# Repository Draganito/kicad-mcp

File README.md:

# kicad-mcp

I built this because I needed a replacement LED panel for my
**Beseler 4×5** enlarger (MILUKA Aristo D2). I had never designed a
PCB, and I did not want to learn KiCad by clicking through menus.

So you keep **KiCad** open. In **Cursor** you tell an assistant what
the board should be — in plain language. It downloads the real JLCPCB
parts, places them, assigns the nets, pours the copper, checks its own
work, and writes the files JLCPCB actually accepts.

This is not a second PCB editor and not “chat, invent a `.kicad_pcb`”.
KiCad stays the source of truth. Every change is **Ctrl+Z**. Nothing
is saved unless you ask.

**Proof it works:** the board that started it —
[contrib/aristo-d2-led-panel](contrib/aristo-d2-led-panel), 109 SK6812
LEDs, 4 layers, designed this way from the first outline to the
ordered Gerbers, manufactured by JLCPCB.

**Work in progress:**
[contrib/aristo-d2-led-panel-v2](contrib/aristo-d2-led-panel-v2) —
112× WS2812B-MINI drop-in. Layout and gerbers only; not a build guide.

**Docs:** [Install on Debian](docs/INSTALL_DEBIAN.md) ·
[Manual (A–Z reference)](docs/MANUAL.md)

---

## Who this is for

Students, hobbyists, makers on **Debian/Ubuntu** who want help with
the boring bits: a LED grid, wire pads, a GND pour, Gerbers that
JLCPCB accepts — without learning a pro tool first.

You still decide the circuit. The assistant must not invent pin
functions — those come from the LCSC / EasyEDA part, and built-in
checks (`check_pins`, `check_placement`, `review_board`) force it to
account for every pin instead of hand-waving.

Skip this if you layout in Altium, only have Windows, or do not want
an assistant in the editor at all.

---

## What you need

- A PC with Debian or Ubuntu (x86-64)
- [KiCad 10](https://www.kicad.org/download/linux/) — not Debian’s
  KiCad 9
- [Cursor](https://cursor.com)
- An LCSC part number when you want a real JLCPCB footprint
  (e.g. `C14663` for an 0603 cap)

---

## Install

1. Download the latest `kicad-mcp_*.deb` from
   **[Releases](https://github.com/Draganito/kicad-mcp/releases)**.
2. Install it:

   ```bash
   sudo apt install ./kicad-mcp_*_amd64.deb
   ```

3. Start KiCad with **`kicad-10`** (comes with the package). Open the
   PCB editor. Enable **Preferences → Plugins → Enable IPC API**, then
   restart KiCad and open the PCB editor again.
4. Copy the Cursor template into the folder you will open:

   ```bash
   cp -a /usr/share/kicad-mcp/cursor-setup/.cursor \
         /usr/share/kicad-mcp/cursor-setup/.cursorignore .
   ```

5. In Cursor, toggle the `kicad-mcp` server off and on.

The autorouter (`kicad-routing-tools_*.deb`, same Releases page) is
**optional**. If you want it: install it too, then run
`kicad-routing-tools-setup` once as your user.

Full walkthrough from a clean machine (AppImage, both packages):
[docs/INSTALL_DEBIAN.md](docs/INSTALL_DEBIAN.md).

---

## First thing to ask

KiCad 10 running, a board open, Cursor on that folder:

> Call `board_summary`.

You want KiCad **10.x**, `has_open_board: true`, and
`net_ipc_persists: true`. If it says 9.x, you started the wrong KiCad
— use `kicad-10`.

Then, in plain language, for example:

> Make a 40 × 30 mm board. Download C14663. Place one cap in the
> middle. Don’t save yet.

Undo is always **Ctrl+Z** in KiCad. The assistant must not save
unless you ask.

---

## How a board usually gets built

1. **Outline** — the yellow Edge.Cuts rectangle *is* the PCB. The pink
   A4 frame is only the drawing sheet.
2. **Parts** — LCSC C-numbers (`download_lcsc_part`), then place or
   a grid (`place_matrix`). Pin names come from EasyEDA, not from
   memory.
3. **Nets** — ratsnest only (`connect_many`). Copper comes later.
4. **Check the nets** — `check_pins`: every pin must be netted or
   explicitly allowed open. No silent floating pins.
5. **Copper** — tracks, vias, 4-layer stack if you need it, GND/5V
   pours. Or named-net autoroute (not GND).
6. **Silk** — `5V` / `GND` / `DATA` next to wire pads. Not on copper.
7. **Check the board** — clearance (`check_drc`), connectivity
   (`check_board`), layout physics (`review_board`).
8. **Order** — `export_manufacturing` writes the JLCPCB zip + BOM +
   pick-and-place. Silk has no U1/C3 (JLCPCB DFM).

Coordinates are millimetres, **+x right, +y up**. Do not edit
`.kicad_pcb` by hand.

The assistant has a small tool list on purpose. The A–Z names live in
the [manual](docs/MANUAL.md).

---

## If something fails

| What you see | Usual cause |
| --- | --- |
| MCP cannot connect | PCB editor closed, or IPC API still off |
| Version 9 / nets empty | System KiCad instead of `kicad-10` |
| Writes refused | Cursor template not copied (needs `--allow-ai-write`) |
| Parts piled in the sheet corner | A bug in pad coordinates — not you; say so |
| AppImage runs, no socket | `.AppImage` started directly instead of `kicad-10` |

More: [manual](docs/MANUAL.md) → “Troubleshooting”.

---

## Build from source

Only if you are changing the Rust code. Makers can stop at the `.deb`.

```bash
cargo test --workspace
cargo build --release -p kicad-mcp
```

Debian package: `dist/make_beta_package.sh` (needs `cargo-deb`).
Point Cursor at the **built binary**, not `cargo run`. After a rebuild,
toggle the MCP server off/on.

Layout of the repo: [docs/architecture.md](docs/architecture.md).

---

## License

[AGPL-3.0-only](LICENSE) — Copyright © 2026 Dragan Bojovic.
See [NOTICE](NOTICE).

KiCad is a separate GPL-3.0 program. This repo only talks to it over
the published IPC API.

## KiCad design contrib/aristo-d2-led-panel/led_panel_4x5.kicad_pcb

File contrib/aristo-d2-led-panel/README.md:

# MILUKA Aristo D2 — an open-source splitgrade system for under $150

A complete splitgrade enlarging system for a **Beseler 4×5**: a
109-LED replacement for the Aristo D2 cold light head, a wireless
receiver, a touch-screen controller (or a free Android app), and a
light meter for dose-based exposure. Everything — hardware, firmware,
CAD, apps — is open source, and the whole system costs **under $150**.

This page is the entry point. It explains how the system works and
walks you through building it, part by part. You do not need to have
designed a PCB or written firmware before — the board is ordered
ready-assembled, the firmware is a prebuilt file you flash once.

## Splitgrade in one minute

Variable-contrast paper reacts to two colors: **green** exposes the
soft (low-contrast) emulsion, **blue** the hard (high-contrast) one.
Classic splitgrade printing means two exposures — one green, one blue
— and the ratio between them sets the contrast. Normally you shuffle
filters under the lens or dial a color head.

This system does it with light itself: the panel carries 109
addressable RGBW LEDs. Green exposure, blue exposure, and a white
channel for focusing — no filters, no filter drawer, nothing moves.
The controller times both exposures and fires them back to back.

## The system at a glance

| Part | Role | Where |
| --- | --- | --- |
| **LED panel** (this folder) | Ø 157 mm, 4-layer PCB, 109× SK6812 RGBW — the light source | Gerbers/BOM/CPL here, JLCPCB builds it |
| **Holder** | 3D-printed shell, replaces the Aristo D2 head, takes the original opal glass | [FreeCAD file](../panel-holder-freecad/panel-holder.FCStd) |
| **XIAO ESP32-S3** | Receiver on the back of the holder, drives the LEDs | [darkroom-enlarger-head](https://github.com/Draganito/darkroom-enlarger-head) firmware |
| **SenseCAP Indicator D1** | 4″ touch controller — exposure, splitgrade ratio, metering (ESP-NOW, no pairing) | [splitgrade-controller-sensecap](https://github.com/Draganito/splitgrade-controller-sensecap) |
| **Android app** | Budget alternative to the SenseCAP, controls the head over BLE | [splitgrade-controller-android](https://github.com/Draganito/splitgrade-controller-android) |
| **TSL2591 sensor** | Light meter for calibration — the controller counts light, not seconds | used by the SenseCAP controller |

The head advertises as `DarkroomTimer`. Both controllers talk to the
same head firmware; you can use either, or both.

## Under $150 — the full bill of materials

List prices, one of each, no shipping or VAT. The panel price is the
JLCPCB assembled board at qty 1.

| Part | USD | Link |
| --- | ---: | --- |
| LED panel, 109× SK6812, JLCPCB SMT | 60.00 | [Gerbers in this folder](led_panel_4x5_gerbers.zip) |
| SenseCAP Indicator D1 (controller) | 49.00 | [seeedstudio.com](https://www.seeedstudio.com/SenseCAP-Indicator-D1-p-5643.html) |
| Seeed XIAO ESP32-S3 (head receiver) | 7.49 | [seeedstudio.com](https://www.seeedstudio.com/XIAO-ESP32S3-p-5627.html) |
| Adafruit TSL2591 (meter) | 6.95 | [adafruit.com/product/1980](https://www.adafruit.com/product/1980) |
| Waveshare 5 V / 5 A PSU, 5.5×2.1 mm | 6.49 | [waveshare.com](https://www.waveshare.com/psu-5v5a-5.5-2.1.htm) |
| 18 AWG DC pigtail 5.5/2.1, screws, solder, PLA+, 5 A fuse | 20.00 | — |
| **Total** | **149.93** | |

### Under $100 — the manual tier

Skip the SenseCAP and the TSL2591 and you have a **manual splitgrade
system for $93.98**: panel, XIAO, PSU and hardware, controlled by the
free [Android app](https://github.com/Draganito/splitgrade-controller-android/releases)
over BLE. You set hard and soft times yourself from test strips — no
metering, no dose calibration, but the same head, the same light and
the same one-button splitgrade exposure. The SenseCAP and sensor can
be added later; nothing has to be rebuilt.

> **App compatibility:** the app is developed and tested on Google
> Pixel phones running GrapheneOS — officially verified on a
> **Pixel 4a** and a **Pixel 9**. Other brands (Samsung, Xiaomi, …)
> ship different BLE stacks and are untested; the app may need
> adjustments there. Testing on more devices is on the roadmap — bug
> reports with the phone model are welcome.

## Build it

### 1. Order the panel

JLCPCB builds and assembles the board from the three files in this
folder — you upload them, click through the options, and a soldered
panel arrives in the mail:

- `led_panel_4x5_gerbers.zip` — Gerbers + drill
- `led_panel_4x5_bom.csv` — BOM (LCSC part numbers)
- `led_panel_4x5_cpl.csv` — pick & place

Every option to click, with screenshots:
[JLCPCB_Order_Guide.pdf](JLCPCB_Order_Guide.pdf). Short version:
4 layers, 1.6 mm FR-4, LeadFree HASL, SMT on the top side.

### 2. Print the holder

The [FreeCAD model](../panel-holder-freecad/panel-holder.FCStd) is a
shell with a 165 mm outer diameter — it drops into the Beseler where
the Aristo D2 head sat. Inside: four M3 bosses the panel screws onto,
holes for the power cable, data/antenna cable, and an SMA antenna.
Print it in PLA+, the chamber walls work best white or lined white.

The **original Aristo opal glass** goes back on top as the diffusor.
With 23 mm of mixing distance between the LEDs and the glass you
cannot see the LED grid, even on large prints.

### 3. Wire it

Three wires go to the panel's labeled pads (2.8 mm pads, 1.4 mm
holes — fits 1 mm² stranded wire):

- **VIN / GND** (top of the board): from a **5.5 / 2.1 mm DC socket**
  (same barrel as the Waveshare 5 V / 5 A PSU). This build uses a
  short pigtail in **18 AWG** — that gauge matters; thinner wire
  drops voltage and heats up at 2–5 A. Keep the run short.
- **DATA** (bottom): from the XIAO's data pin (GPIO 5 / pin D4),
  through the on-board level shifter to the first LED. The data
  wire can be thinner than the power pair.

Put an **inline blade fuse on the +5 V lead, before VIN**. Do not
feed the pad unfused. A 5 A ATC/ATO fuse matches the PSU and the
panel's worst-case load. Cut the holder's red loop, splice it in
series on the positive wire only, then close the cap.

The XIAO sits on the **back** of the holder and taps 5 V and GND with
thin wires. Never route the LED current through the XIAO — the panel
draws up to 2.3 A in printing modes (green+blue or white), and the
theoretical everything-on maximum is 5 A / 25 W. That worst case never
occurs while printing, which is why the 5 A supply is enough. The load
table is printed on the back silk of the panel.

### 4. Flash the head

Download the ready-made `.bin` from the
[firmware releases](https://github.com/Draganito/darkroom-enlarger-head/releases)
and follow
[FLASH.md](https://github.com/Draganito/darkroom-enlarger-head/blob/main/FLASH.md) —
on Debian it is `apt install esptool` and one `write_flash` command.
No toolchain, no IDE.

The firmware boots with the right defaults for this panel: **109 LEDs
on GPIO 5**. It listens on ESP-NOW and BLE at the same time.

### 5. Pick a controller

**[SenseCAP Indicator D1](https://github.com/Draganito/splitgrade-controller-sensecap)**
is the primary tier: 4″ touch screen, ESP-NOW (instant, no pairing),
metering and calibration with the TSL2591. Seeed wiki:
[hands-on demo](https://wiki.seeedstudio.com/SenseCAP_Indicator_Application_LoRaWAN/#hands-on-demo).

**[Android app](https://github.com/Draganito/splitgrade-controller-android/releases)**
is the budget tier: a free APK over BLE, same head, no sensor. Sideload
steps: [INSTALL.md](https://github.com/Draganito/splitgrade-controller-android/blob/main/INSTALL.md).

How to connect (the home screen does **not** scan by itself):

1. Power the head from the 5 V supply. The XIAO advertises as
   `DarkroomTimer`.
2. On the phone: Bluetooth on, allow **Nearby devices** when the app
   asks.
3. **Do not pair** `DarkroomTimer` in Android Bluetooth settings. A
   system pair breaks the app after a firmware flash.
4. Open **miluka Splitgrade Controller**.
5. Hold **Focus** for 3 seconds → **Settings**.
6. Tap **Scan for devices**, then tap **DarkroomTimer**.
7. LED count and DATA pin default to **109 / GPIO 5** (this panel).
   Change them only for a different board, then **Save**.

A crossed-out Bluetooth icon on the timer screen means “not connected
yet” — that is normal until you finish step 6. Next launch the app
tries the last device by itself.

### 6. Calibrate and print

Plug the Adafruit TSL2591 into the SenseCAP D1 with one off-the-shelf
4-wire cable — no soldering:

- SenseCAP end: **Grove**, JST-PH **2.0 mm**, 4-pin (the lower Grove
  socket on the back of the D1)
- Sensor end: **STEMMA QT / Qwiic**, JST-SH **1.0 mm**, 4-pin

That cable is sold as **Grove → STEMMA QT / Qwiic**. It carries I2C
(SDA, SCL) plus power and GND. A Grove-to-Grove lead will not fit the
Adafruit board; a QT-to-QT lead will not fit the SenseCAP.

The controller does not store times — it stores a **target dose**
(intensity × time) per color, once per paper/developer combination.
Every print then gets a fresh measurement, and the time is computed
as `time = stored dose / measured intensity`. LED warm-up, supply
drift, a new enlarger height, a different aperture — all of it is
absorbed by the measurement instead of shifting your print.

**Calibrate once per paper/developer** — you need a **Stouffer
T2115** transmission stepwedge (21 steps, ½ stop per step; the
firmware assumes exactly this geometry):

1. Put the stepwedge in the negative carrier, the sensor on the
   baseboard.
2. Hold **MEAS BLK** ~3 seconds → the hidden calibration screen.
3. Blue side: tap **READ REF** (captures the current blue
   intensity), expose a real test print for the shown **TEST TIME**,
   develop it.
4. Find the step where the tone first reaches your target — for blue
   the first solid black — and dial that number in with **STEP +/-**.
   Tap **SAVE**.
5. Repeat for the green side; the target there is the first visible
   grey (green sets the highlights).

**Every print after that:**

1. Negative in, **FOCUS**, frame, set the aperture.
2. Sensor on the **clear film edge between frames** — not on the
   image. That is the stable, repeatable reading.
3. Tap **MEAS BLK**, then **MEAS LIT** — hard and soft times appear.
4. **EXPOSURE**.
5. Judge the print. Fine-tune with **HARD +/-** (shadows/contrast)
   and **SOFT +/-** (highlights) — do not measure again unless you
   changed height or aperture, because a new measurement overwrites
   the hand-tuned times.

**EXPOSURE** always works as an immediate stop, whatever is running.

For advanced users there is an optional **cross factor** (a hidden
screen, off by default): VC paper's soft emulsion keeps its full blue
sensitivity, so a long hard/blue exposure also pushes the highlights.
A positive cross factor subtracts a fraction of the hard time from
the soft time to compensate — an original development of this
project, tuned per paper with real test prints. Details in the
[controller docs](https://github.com/Draganito/splitgrade-controller-sensecap).

> **Status: test and development phase.** The sensor system, the
> dose-based calibration logic and the cross factor work on the
> bench, but many darkroom tests are still ahead. Do not treat the
> metering side as a finished product yet — expect to make test
> prints and to update firmware as it matures. The LED panel itself
> and the timer/exposure side are built and tested.

## The panel, technically

- Ø 157 mm round, 4-layer, 1.6 mm FR-4. Layer stack: signal + GND
  pour on top, solid 5 V plane, solid GND plane, GND on the bottom.
- 109× SK6812 RGBW (LCSC C5348912) on a 12.7 mm grid, each with a
  local 100 nF cap; two 220 µF polymer bulk caps at the power entry.
- SN74AHCT1G125 level shifter and 330 Ω series resistor on DATA, TVS
  diode across the input — the usual addressable-LED hygiene, already
  on the board.
- Wire pads instead of connectors: solder three wires and done.
- Four M3 mounting holes with copper keepouts sized for screw heads.

To inspect or adapt the design: KiCad **10**, open
`led_panel_4x5.kicad_pro`. All footprints live in
`jlcpcb_parts.pretty/` (already in the project library table). Do not
edit the `.kicad_pcb` in a text editor.

## How this board was designed

I had never designed a PCB. The panel was built by telling an AI
assistant what the board should be — it fetched the real JLCPCB
parts, placed the 109 LEDs, poured the copper, checked its own work,
and exported these manufacturing files. That tool is the parent repo:
[kicad-mcp](../../README.md). If you want a panel for a different
enlarger, that is the way to make one.

## Photos & video

On the Beseler, with the XIAO on the back of the holder:

https://github.com/user-attachments/assets/cf3984b5-ae27-4c1a-a5dd-19e20b47ff94

The Android app driving the head over BLE — focus, split-grade
exposure, settings:

https://github.com/user-attachments/assets/70728c96-0126-4f3b-ad37-9e4ec7c04c5c

Factory SMT view from the JLCPCB order:

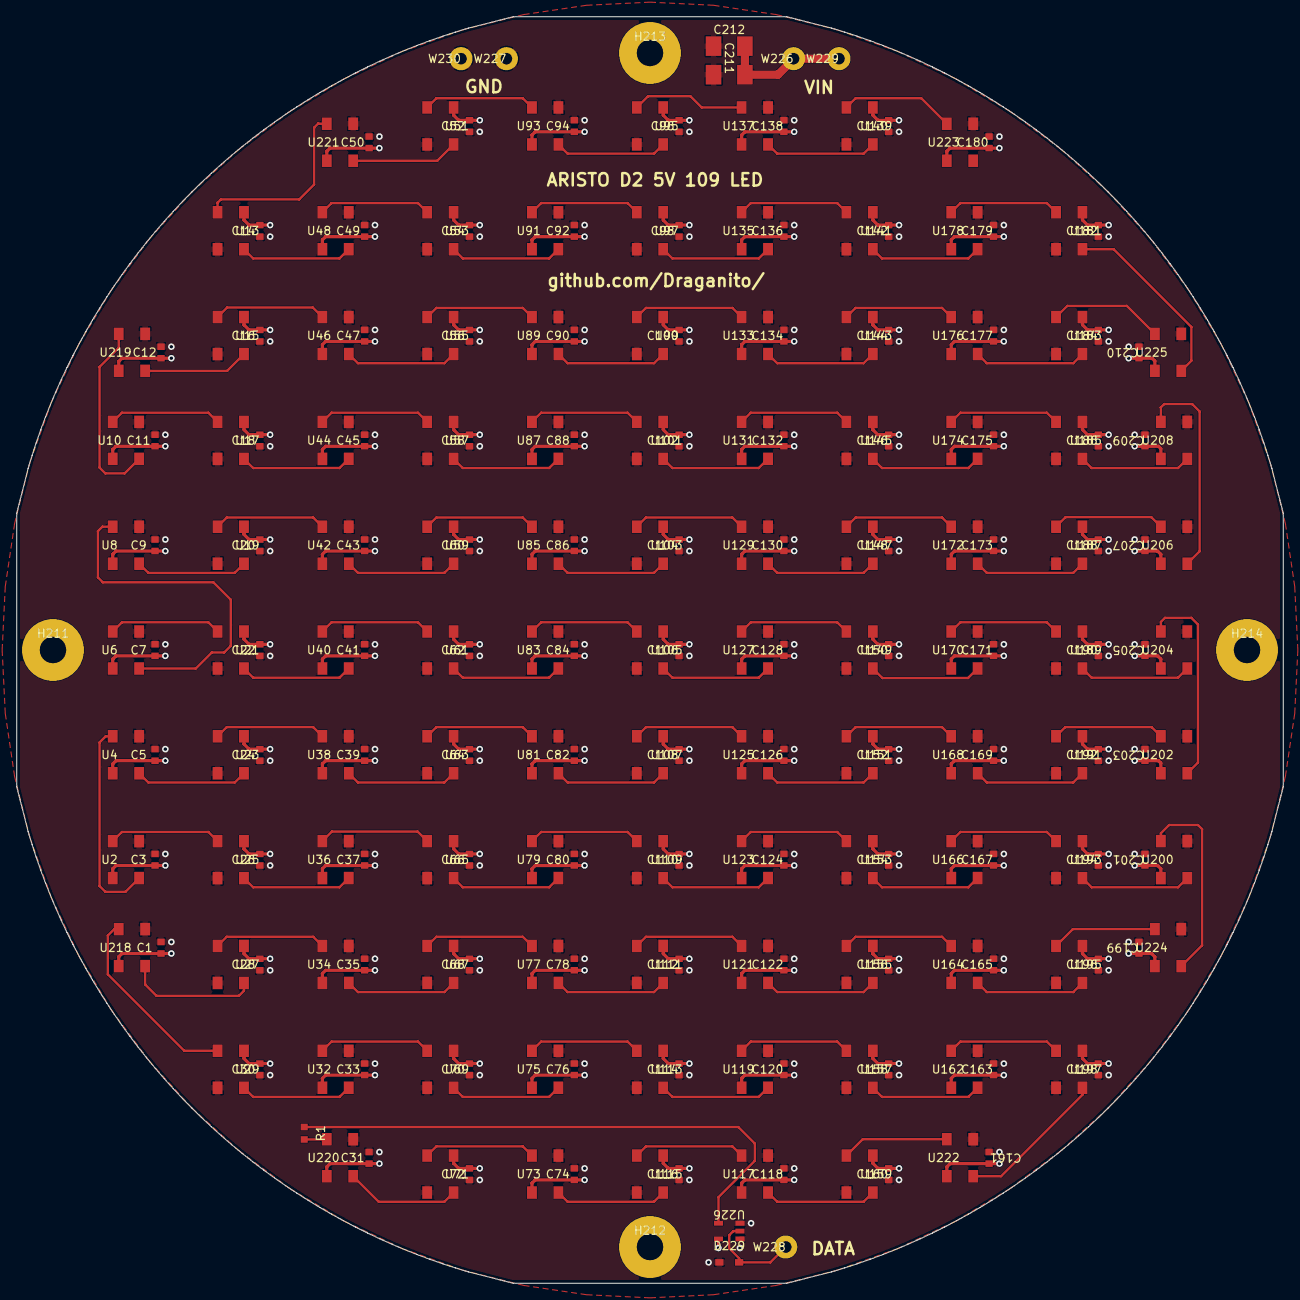
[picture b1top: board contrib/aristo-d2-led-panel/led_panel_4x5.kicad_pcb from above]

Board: 4 copper layers, 153.5 x 153.5 mm, 232 parts (0 on the bottom side), 113 nets.

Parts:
C1, C3, C5, C7, C9, C11, C12, C14, C16, C18, C20, C22, C24, C26, C28, C30, C31, C33, C35, C37, C39, C41, C43, C45, C47, C49, C50, C52, C54, C56, C58, C60, C62, C64, C66, C68, C70, C72, C74, C76, C78, C80, C82, C84, C86, C88, C90, C92, C94, C96, C98, C100, C102, C104, C106, C108, C110, C112, C114, C116, C118, C120, C122, C124, C126, C128, C130, C132, C134, C136, C138, C140, C142, C144, C146, C148, C150, C152, C154, C156, C158, C160, C161, C163, C165, C167, C169, C171, C173, C175, C177, C179, C180, C182, C184, C186, C188, C190, C192, C194, C196, C198, C199, C201, C203, C205, C207, C209, C210: C14663_C0603
C211, C212: C79111_CAP-SMD_L3.5-W2.8-R-RD
D229: C502527_SOD-323_L1.8-W1.3-LS2.5-FD
H211, H212, H213, H214: MountingHole_M3_NPTH
R1: C23138_R0603
U2, U4, U6, U8, U10, U13, U15, U17, U19, U21, U23, U25, U27, U29, U32, U34, U36, U38, U40, U42, U44, U46, U48, U51, U53, U55, U57, U59, U61, U63, U65, U67, U69, U71, U73, U75, U77, U79, U81, U83, U85, U87, U89, U91, U93, U95, U97, U99, U101, U103, U105, U107, U109, U111, U113, U115, U117, U119, U121, U123, U125, U127, U129, U131, U133, U135, U137, U139, U141, U143, U145, U147, U149, U151, U153, U155, U157, U159, U162, U164, U166, U168, U170, U172, U174, U176, U178, U181, U183, U185, U187, U189, U191, U193, U195, U197, U200, U202, U204, U206, U208, U218, U219, U220, U221, U222, U223, U224, U225: C5348912_LED-SMD_4P-L5.0-W4.9-BR
U226: C7484_SOT-23-5_L3.0-W1.7-P0.95-LS2.8-BR
W226, W227, W228, W229, W230: WirePad_PTH_2.8_1.4

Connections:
5V: C1.1, C3.1, C5.1, C7.1, C9.1, C11.1, C12.1, C14.2, C16.2, C18.2, C20.2, C22.2, C24.2, C26.2, C28.2, C30.2, C31.1, C33.1, C35.1, C37.1, C39.1, C41.1, C43.1, C45.1, C47.1, C49.1, C50.1, C52.2, C54.2, C56.2, C58.2, C60.2, C62.2, C64.2, C66.2, C68.2, C70.2, C72.2, C74.1, C76.1, C78.1, C80.1, C82.1, C84.1, C86.1, C88.1, C90.1, C92.1, C94.1, C96.2, C98.2, C100.2, C102.2, C104.2, C106.2, C108.2, C110.2, C112.2, C114.2, C116.2, C118.1, C120.1, C122.1, C124.1, C126.1, C128.1, C130.1, C132.1, C134.1, C136.1, C138.1, C140.2, C142.2, C144.2, C146.2, C148.2, C150.2, C152.2, C154.2, C156.2, C158.2, C160.2, C161.2, C163.1, C165.1, C167.1, C169.1, C171.1, C173.1, C175.1, C177.1, C179.1, C180.1, C182.2, C184.2, C186.2, C188.2, C190.2, C192.2, C194.2, C196.2, C198.2, C199.1, C201.1, C203.1, C205.1, C207.1, C209.1, C210.1, C211.1, C212.1, U2.3, U4.3, U6.3, U8.3, U10.3, U13.3, U15.3, U17.3, U19.3, U21.3, U23.3, U25.3, U27.3, U29.3, U32.3, U34.3, U36.3, U38.3, U40.3, U42.3, U44.3, U46.3, U48.3, U51.3, U53.3, U55.3, U57.3, U59.3, U61.3, U63.3, U65.3, U67.3, U69.3, U71.3, U73.3, U75.3, U77.3, U79.3, U81.3, U83.3, U85.3, U87.3, U89.3, U91.3, U93.3, U95.3, U97.3, U99.3, U101.3, U103.3, U105.3, U107.3, U109.3, U111.3, U113.3, U115.3, U117.3, U119.3, U121.3, U123.3, U125.3, U127.3, U129.3, U131.3, U133.3, U135.3, U137.3, U139.3, U141.3, U143.3, U145.3, U147.3, U149.3, U151.3, U153.3, U155.3, U157.3, U159.3, U162.3, U164.3, U166.3, U168.3, U170.3, U172.3, U174.3, U176.3, U178.3, U181.3, U183.3, U185.3, U187.3, U189.3, U191.3, U193.3, U195.3, U197.3, U200.3, U202.3, U204.3, U206.3, U208.3, U218.3, U219.3, U220.3, U221.3, U222.3, U223.3, U224.3, U225.3, U226.5, W226.1, W229.1
DATA_IN: D229.2, U226.2, W228.1
GND: C1.2, C3.2, C5.2, C7.2, C9.2, C11.2, C12.2, C14.1, C16.1, C18.1, C20.1, C22.1, C24.1, C26.1, C28.1, C30.1, C31.2, C33.2, C35.2, C37.2, C39.2, C41.2, C43.2, C45.2, C47.2, C49.2, C50.2, C52.1, C54.1, C56.1, C58.1, C60.1, C62.1, C64.1, C66.1, C68.1, C70.1, C72.1, C74.2, C76.2, C78.2, C80.2, C82.2, C84.2, C86.2, C88.2, C90.2, C92.2, C94.2, C96.1, C98.1, C100.1, C102.1, C104.1, C106.1, C108.1, C110.1, C112.1, C114.1, C116.1, C118.2, C120.2, C122.2, C124.2, C126.2, C128.2, C130.2, C132.2, C134.2, C136.2, C138.2, C140.1, C142.1, C144.1, C146.1, C148.1, C150.1, C152.1, C154.1, C156.1, C158.1, C160.1, C161.1, C163.2, C165.2, C167.2, C169.2, C171.2, C173.2, C175.2, C177.2, C179.2, C180.2, C182.1, C184.1, C186.1, C188.1, C190.1, C192.1, C194.1, C196.1, C198.1, C199.2, C201.2, C203.2, C205.2, C207.2, C209.2, C210.2, C211.2, C212.2, D229.1, U2.1, U4.1, U6.1, U8.1, U10.1, U13.1, U15.1, U17.1, U19.1, U21.1, U23.1, U25.1, U27.1, U29.1, U32.1, U34.1, U36.1, U38.1, U40.1, U42.1, U44.1, U46.1, U48.1, U51.1, U53.1, U55.1, U57.1, U59.1, U61.1, U63.1, U65.1, U67.1, U69.1, U71.1, U73.1, U75.1, U77.1, U79.1, U81.1, U83.1, U85.1, U87.1, U89.1, U91.1, U93.1, U95.1, U97.1, U99.1, U101.1, U103.1, U105.1, U107.1, U109.1, U111.1, U113.1, U115.1, U117.1, U119.1, U121.1, U123.1, U125.1, U127.1, U129.1, U131.1, U133.1, U135.1, U137.1, U139.1, U141.1, U143.1, U145.1, U147.1, U149.1, U151.1, U153.1, U155.1, U157.1, U159.1, U162.1, U164.1, U166.1, U168.1, U170.1, U172.1, U174.1, U176.1, U178.1, U181.1, U183.1, U185.1, U187.1, U189.1, U191.1, U193.1, U195.1, U197.1, U200.1, U202.1, U204.1, U206.1, U208.1, U218.1, U219.1, U220.1, U221.1, U222.1, U223.1, U224.1, U225.1, U226.1, U226.3, W227.1, W230.1
Net1: R1.2, U220.2
Net2: U71.2, U220.4
Net3: U71.4, U73.2
Net4: U73.4, U115.2
Net5: U115.4, U117.2
Net6: U117.4, U159.2
Net7: U159.4, U222.2
Net8: U197.2, U222.4
Net9: U162.2, U197.4
Net10: U157.2, U162.4
Net11: U119.2, U157.4
Net12: U113.2, U119.4
Net13: U75.2, U113.4
Net14: U69.2, U75.4
Net15: U32.2, U69.4
Net16: U29.2, U32.4
Net17: U29.4, U218.2
Net18: U27.2, U218.4
Net19: U27.4, U34.2
Net20: U34.4, U67.2
Net21: U67.4, U77.2
Net22: U77.4, U111.2
Net23: U111.4, U121.2
Net24: U121.4, U155.2
Net25: U155.4, U164.2
Net26: U164.4, U195.2
Net27: U195.4, U224.2
Net28: U200.2, U224.4
Net29: U193.2, U200.4
Net30: U166.2, U193.4
Net31: U153.2, U166.4
Net32: U123.2, U153.4
Net33: U109.2, U123.4
Net34: U79.2, U109.4
Net35: U65.2, U79.4
Net36: U36.2, U65.4
Net37: U25.2, U36.4
Net38: U2.2, U25.4
Net39: U2.4, U4.2
Net40: U4.4, U23.2
Net41: U23.4, U38.2
Net42: U38.4, U63.2
Net43: U63.4, U81.2
Net44: U81.4, U107.2
Net45: U107.4, U125.2
Net46: U125.4, U151.2
Net47: U151.4, U168.2
Net48: U168.4, U191.2
Net49: U191.4, U202.2
Net50: U202.4, U204.2
Net51: U189.2, U204.4
Net52: U170.2, U189.4
Net53: U149.2, U170.4
Net54: U127.2, U149.4
Net55: U105.2, U127.4
Net56: U83.2, U105.4
Net57: U61.2, U83.4
Net58: U40.2, U61.4
Net59: U21.2, U40.4
Net60: U6.2, U21.4
Net61: U6.4, U8.2
Net62: U8.4, U19.2
Net63: U19.4, U42.2
Net64: U42.4, U59.2
Net65: U59.4, U85.2
Net66: U85.4, U103.2
Net67: U103.4, U129.2
Net68: U129.4, U147.2
Net69: U147.4, U172.2
Net70: U172.4, U187.2
Net71: U187.4, U206.2
Net72: U206.4, U208.2
Net73: U185.2, U208.4
Net74: U174.2, U185.4
Net75: U145.2, U174.4
Net76: U131.2, U145.4
Net77: U101.2, U131.4
Net78: U87.2, U101.4
Net79: U57.2, U87.4
Net80: U44.2, U57.4
Net81: U17.2, U44.4
Net82: U10.2, U17.4
Net83: U10.4, U219.2
Net84: U15.2, U219.4
Net85: U15.4, U46.2
Net86: U46.4, U55.2
Net87: U55.4, U89.2
Net88: U89.4, U99.2
Net89: U99.4, U133.2
Net90: U133.4, U143.2
Net91: U143.4, U176.2
Net92: U176.4, U183.2
Net93: U183.4, U225.2
Net94: U181.2, U225.4
Net95: U178.2, U181.4
Net96: U141.2, U178.4
Net97: U135.2, U141.4
Net98: U97.2, U135.4
Net99: U91.2, U97.4
Net100: U53.2, U91.4
Net101: U48.2, U53.4
Net102: U13.2, U48.4
Net103: U13.4, U221.2
Net104: U51.2, U221.4
Net105: U51.4, U93.2
Net106: U93.4, U95.2
Net107: U95.4, U137.2
Net108: U137.4, U139.2
Net109: U139.4, U223.2
Net_R1_2: R1.1, U226.4

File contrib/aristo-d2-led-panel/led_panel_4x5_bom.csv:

Comment,Designator,Footprint,LCSC Part #
C14663_C0603,"C1, C100, C102, C104, C106, C108, C11, C110, C112, C114, C116, C118, C12, C120, C122, C124, C126, C128, C130, C132, C134, C136, C138, C14, C140, C142, C144, C146, C148, C150, C152, C154, C156, C158, C16, C160, C161, C163, C165, C167, C169, C171, C173, C175, C177, C179, C18, C180, C182, C184, C186, C188, C190, C192, C194, C196, C198, C199, C20, C201, C203, C205, C207, C209, C210, C22, C24, C26, C28, C3, C30, C31, C33, C35, C37, C39, C41, C43, C45, C47, C49, C5, C50, C52, C54, C56, C58, C60, C62, C64, C66, C68, C7, C70, C72, C74, C76, C78, C80, C82, C84, C86, C88, C9, C90, C92, C94, C96, C98",C0603,C14663
C79111_CAP-SMD_L3.5-W2.8-R-RD,"C211, C212",CAP-SMD_L3.5-W2.8-R-RD,C79111
C5348912_LED-SMD_4P-L5.0-W4.9-BR,"U10, U101, U103, U105, U107, U109, U111, U113, U115, U117, U119, U121, U123, U125, U127, U129, U13, U131, U133, U135, U137, U139, U141, U143, U145, U147, U149, U15, U151, U153, U155, U157, U159, U162, U164, U166, U168, U17, U170, U172, U174, U176, U178, U181, U183, U185, U187, U189, U19, U191, U193, U195, U197, U2, U200, U202, U204, U206, U208, U21, U218, U219, U220, U221, U222, U223, U224, U225, U23, U25, U27, U29, U32, U34, U36, U38, U4, U40, U42, U44, U46, U48, U51, U53, U55, U57, U59, U6, U61, U63, U65, U67, U69, U71, U73, U75, U77, U79, U8, U81, U83, U85, U87, U89, U91, U93, U95, U97, U99",LED-SMD_4P-L5.0-W4.9-BR,C5348912
C23138_R0603,R1,R0603,C23138
C502527_SOD-323_L1.8-W1.3-LS2.5-FD,D229,SOD-323_L1.8-W1.3-LS2.5-FD,C502527
C7484_SOT-23-5_L3.0-W1.7-P0.95-LS2.8-BR,U226,SOT-23-5_L3.0-W1.7-P0.95-LS2.8-BR,C7484

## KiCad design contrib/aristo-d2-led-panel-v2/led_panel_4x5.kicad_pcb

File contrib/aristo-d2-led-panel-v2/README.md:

# MILUKA Aristo D2 LED panel v2 — work in progress

**Work in progress.** Do not order this board yet. There is no build
guide here.

The shipping panel (109× SK6812, BOM, order walkthrough) is
[aristo-d2-led-panel](../aristo-d2-led-panel).

This folder is the next drop-in head: Ø 157 mm, 4-layer, **112×
WorldSemi WS2812B-MINI-JT01/W** (LCSC `C42417599`). KiCad files,
gerbers, BOM and CPL are in the tree so the layout can be reviewed.
Firmware notes, photos of *this* revision, and the order walkthrough
are not ready.

| File | What |
| --- | --- |
| [led_panel_4x5.kicad_pcb](led_panel_4x5.kicad_pcb) | PCB |
| [led_panel_4x5_gerbers.zip](led_panel_4x5_gerbers.zip) | JLCPCB gerbers (includes back silk datasheet) |
| [led_panel_4x5_bom.csv](led_panel_4x5_bom.csv) | BOM |
| [led_panel_4x5_cpl.csv](led_panel_4x5_cpl.csv) | pick-and-place |

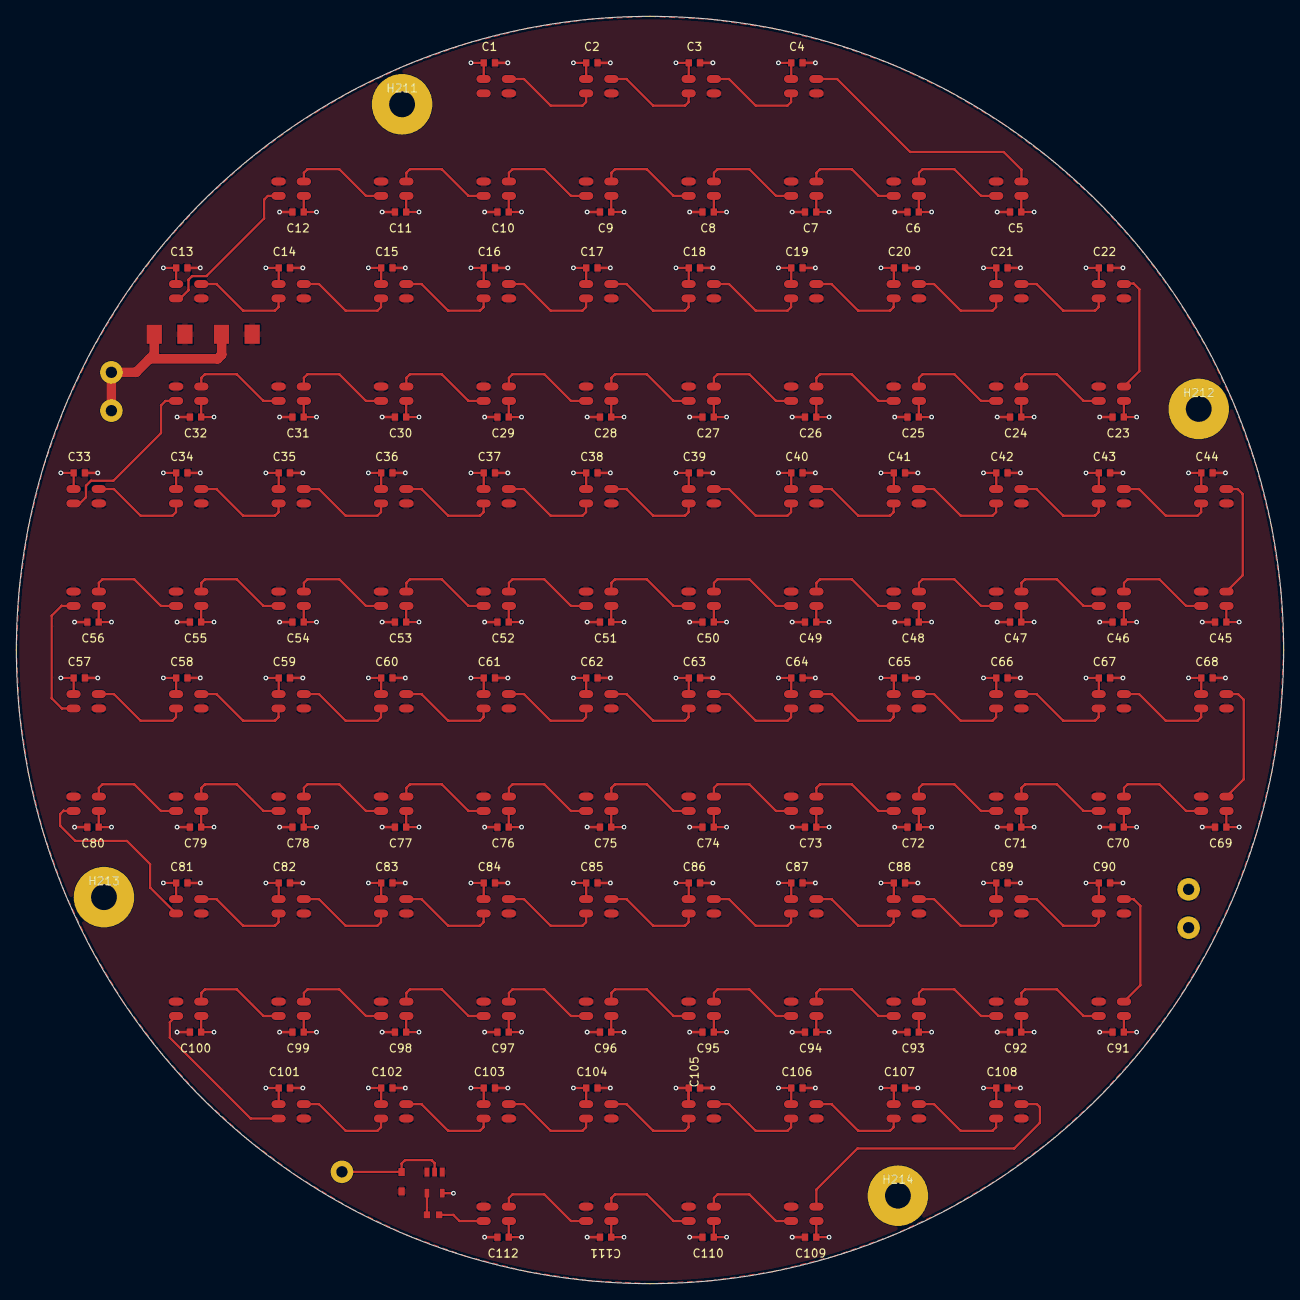
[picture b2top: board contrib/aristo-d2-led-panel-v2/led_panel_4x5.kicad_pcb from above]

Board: 4 copper layers, 157.0 x 157.0 mm, 238 parts (0 on the bottom side), 116 nets.

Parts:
C1, C2, C3, C4, C5, C6, C7, C8, C9, C10, C11, C12, C13, C14, C15, C16, C17, C18, C19, C20, C21, C22, C23, C24, C25, C26, C27, C28, C29, C30, C31, C32, C33, C34, C35, C36, C37, C38, C39, C40, C41, C42, C43, C44, C45, C46, C47, C48, C49, C50, C51, C52, C53, C54, C55, C56, C57, C58, C59, C60, C61, C62, C63, C64, C65, C66, C67, C68, C69, C70, C71, C72, C73, C74, C75, C76, C77, C78, C79, C80, C81, C82, C83, C84, C85, C86, C87, C88, C89, C90, C91, C92, C93, C94, C95, C96, C97, C98, C99, C100, C101, C102, C103, C104, C105, C106, C107, C108, C109, C110, C111, C112: C14663_C0603
C211, C212: C79111_CAP-SMD_L3.5-W2.8-R-RD
D229: C502527_SOD-323_L1.8-W1.3-LS2.5-FD
H211, H212, H213, H214: MountingHole_M3_NPTH
R1: C23138_R0603
U1, U2, U3, U4, U5, U6, U7, U8, U9, U10, U11, U12, U13, U14, U15, U16, U17, U18, U19, U20, U21, U22, U23, U24, U25, U26, U27, U28, U29, U30, U31, U32, U33, U34, U35, U36, U37, U38, U39, U40, U41, U42, U43, U44, U45, U46, U47, U48, U49, U50, U51, U52, U53, U54, U55, U56, U57, U58, U59, U60, U61, U62, U63, U64, U65, U66, U67, U68, U69, U70, U71, U72, U73, U74, U75, U76, U77, U78, U79, U80, U81, U82, U83, U84, U85, U86, U87, U88, U89, U90, U91, U92, U93, U94, U95, U96, U97, U98, U99, U100, U101, U102, U103, U104, U105, U106, U107, U108, U109, U110, U111, U112: C42417599_LED-SMD_4P-L3.5-W3.5-TL_WS2812B_WS
U226: C7484_SOT-23-5_L3.0-W1.7-P0.95-LS2.8-BR
W226, W227, W228, W229, W230: WirePad_PTH_2.8_1.4

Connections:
5V: C1.1, C2.1, C3.1, C4.1, C5.1, C6.1, C7.1, C8.1, C9.1, C10.1, C11.1, C12.1, C13.1, C14.1, C15.1, C16.1, C17.1, C18.1, C19.1, C20.1, C21.1, C22.1, C23.1, C24.1, C25.1, C26.1, C27.1, C28.1, C29.1, C30.1, C31.1, C32.1, C33.1, C34.1, C35.1, C36.1, C37.1, C38.1, C39.1, C40.1, C41.1, C42.1, C43.1, C44.1, C45.1, C46.1, C47.1, C48.1, C49.1, C50.1, C51.1, C52.1, C53.1, C54.1, C55.1, C56.1, C57.1, C58.1, C59.1, C60.1, C61.1, C62.1, C63.1, C64.1, C65.1, C66.1, C67.1, C68.1, C69.1, C70.1, C71.1, C72.1, C73.1, C74.1, C75.1, C76.1, C77.1, C78.1, C79.1, C80.1, C81.1, C82.1, C83.1, C84.1, C85.1, C86.1, C87.1, C88.1, C89.1, C90.1, C91.1, C92.1, C93.1, C94.1, C95.1, C96.1, C97.1, C98.1, C99.1, C100.1, C101.1, C102.1, C103.1, C104.1, C105.1, C106.1, C107.1, C108.1, C109.1, C110.1, C111.1, C112.1, C211.1, C212.1, U1.1, U2.1, U3.1, U4.1, U5.1, U6.1, U7.1, U8.1, U9.1, U10.1, U11.1, U12.1, U13.1, U14.1, U15.1, U16.1, U17.1, U18.1, U19.1, U20.1, U21.1, U22.1, U23.1, U24.1, U25.1, U26.1, U27.1, U28.1, U29.1, U30.1, U31.1, U32.1, U33.1, U34.1, U35.1, U36.1, U37.1, U38.1, U39.1, U40.1, U41.1, U42.1, U43.1, U44.1, U45.1, U46.1, U47.1, U48.1, U49.1, U50.1, U51.1, U52.1, U53.1, U54.1, U55.1, U56.1, U57.1, U58.1, U59.1, U60.1, U61.1, U62.1, U63.1, U64.1, U65.1, U66.1, U67.1, U68.1, U69.1, U70.1, U71.1, U72.1, U73.1, U74.1, U75.1, U76.1, U77.1, U78.1, U79.1, U80.1, U81.1, U82.1, U83.1, U84.1, U85.1, U86.1, U87.1, U88.1, U89.1, U90.1, U91.1, U92.1, U93.1, U94.1, U95.1, U96.1, U97.1, U98.1, U99.1, U100.1, U101.1, U102.1, U103.1, U104.1, U105.1, U106.1, U107.1, U108.1, U109.1, U110.1, U111.1, U112.1, U226.5, W226.1, W229.1
DATA: R1.2, U112.4
DATA_1: U1.4, U2.2
DATA_2: U2.4, U3.2
DATA_3: U3.4, U4.2
DATA_4: U4.4, U5.2
DATA_5: U5.4, U6.2
DATA_6: U6.4, U7.2
DATA_7: U7.4, U8.2
DATA_8: U8.4, U9.2
DATA_9: U9.4, U10.2
DATA_10: U10.4, U11.2
DATA_11: U11.4, U12.2
DATA_12: U12.4, U13.2
DATA_13: U13.4, U14.2
DATA_14: U14.4, U15.2
DATA_15: U15.4, U16.2
DATA_16: U16.4, U17.2
DATA_17: U17.4, U18.2
DATA_18: U18.4, U19.2
DATA_19: U19.4, U20.2
DATA_20: U20.4, U21.2
DATA_21: U21.4, U22.2
DATA_22: U22.4, U23.2
DATA_23: U23.4, U24.2
DATA_24: U24.4, U25.2
DATA_25: U25.4, U26.2
DATA_26: U26.4, U27.2
DATA_27: U27.4, U28.2
DATA_28: U28.4, U29.2
DATA_29: U29.4, U30.2
DATA_30: U30.4, U31.2
DATA_31: U31.4, U32.2
DATA_32: U32.4, U33.2
DATA_33: U33.4, U34.2
DATA_34: U34.4, U35.2
DATA_35: U35.4, U36.2
DATA_36: U36.4, U37.2
DATA_37: U37.4, U38.2
DATA_38: U38.4, U39.2
DATA_39: U39.4, U40.2
DATA_40: U40.4, U41.2
DATA_41: U41.4, U42.2
DATA_42: U42.4, U43.2
DATA_43: U43.4, U44.2
DATA_44: U44.4, U45.2
DATA_45: U45.4, U46.2
DATA_46: U46.4, U47.2
DATA_47: U47.4, U48.2
DATA_48: U48.4, U49.2
DATA_49: U49.4, U50.2
DATA_50: U50.4, U51.2
DATA_51: U51.4, U52.2
DATA_52: U52.4, U53.2
DATA_53: U53.4, U54.2
DATA_54: U54.4, U55.2
DATA_55: U55.4, U56.2
DATA_56: U56.4, U57.2
DATA_57: U57.4, U58.2
DATA_58: U58.4, U59.2
DATA_59: U59.4, U60.2
DATA_60: U60.4, U61.2
DATA_61: U61.4, U62.2
DATA_62: U62.4, U63.2
DATA_63: U63.4, U64.2
DATA_64: U64.4, U65.2
DATA_65: U65.4, U66.2
DATA_66: U66.4, U67.2
DATA_67: U67.4, U68.2
DATA_68: U68.4, U69.2
DATA_69: U69.4, U70.2
DATA_70: U70.4, U71.2
DATA_71: U71.4, U72.2
DATA_72: U72.4, U73.2
DATA_73: U73.4, U74.2
DATA_74: U74.4, U75.2
DATA_75: U75.4, U76.2
DATA_76: U76.4, U77.2
DATA_77: U77.4, U78.2
DATA_78: U78.4, U79.2
DATA_79: U79.4, U80.2
DATA_80: U80.4, U81.2
DATA_81: U81.4, U82.2
DATA_82: U82.4, U83.2
DATA_83: U83.4, U84.2
DATA_84: U84.4, U85.2
DATA_85: U85.4, U86.2
DATA_86: U86.4, U87.2
DATA_87: U87.4, U88.2
DATA_88: U88.4, U89.2
DATA_89: U89.4, U90.2
DATA_90: U90.4, U91.2
DATA_91: U91.4, U92.2
DATA_92: U92.4, U93.2
DATA_93: U93.4, U94.2
DATA_94: U94.4, U95.2
DATA_95: U95.4, U96.2
DATA_96: U96.4, U97.2
DATA_97: U97.4, U98.2
DATA_98: U98.4, U99.2
DATA_99: U99.4, U100.2
DATA_100: U100.4, U101.2
DATA_101: U101.4, U102.2
DATA_102: U102.4, U103.2
DATA_103: U103.4, U104.2
DATA_104: U104.4, U105.2
DATA_105: U105.4, U106.2
DATA_106: U106.4, U107.2
DATA_107: U107.4, U108.2
DATA_108: U108.4, U109.2
DATA_109: U109.4, U110.2
DATA_110: U110.4, U111.2
DATA_111: U111.4, U112.2
DATA_IN: D229.2, U226.2, W228.1
GND: C1.2, C2.2, C3.2, C4.2, C5.2, C6.2, C7.2, C8.2, C9.2, C10.2, C11.2, C12.2, C13.2, C14.2, C15.2, C16.2, C17.2, C18.2, C19.2, C20.2, C21.2, C22.2, C23.2, C24.2, C25.2, C26.2, C27.2, C28.2, C29.2, C30.2, C31.2, C32.2, C33.2, C34.2, C35.2, C36.2, C37.2, C38.2, C39.2, C40.2, C41.2, C42.2, C43.2, C44.2, C45.2, C46.2, C47.2, C48.2, C49.2, C50.2, C51.2, C52.2, C53.2, C54.2, C55.2, C56.2, C57.2, C58.2, C59.2, C60.2, C61.2, C62.2, C63.2, C64.2, C65.2, C66.2, C67.2, C68.2, C69.2, C70.2, C71.2, C72.2, C73.2, C74.2, C75.2, C76.2, C77.2, C78.2, C79.2, C80.2, C81.2, C82.2, C83.2, C84.2, C85.2, C86.2, C87.2, C88.2, C89.2, C90.2, C91.2, C92.2, C93.2, C94.2, C95.2, C96.2, C97.2, C98.2, C99.2, C100.2, C101.2, C102.2, C103.2, C104.2, C105.2, C106.2, C107.2, C108.2, C109.2, C110.2, C111.2, C112.2, C211.2, C212.2, D229.1, U1.3, U2.3, U3.3, U4.3, U5.3, U6.3, U7.3, U8.3, U9.3, U10.3, U11.3, U12.3, U13.3, U14.3, U15.3, U16.3, U17.3, U18.3, U19.3, U20.3, U21.3, U22.3, U23.3, U24.3, U25.3, U26.3, U27.3, U28.3, U29.3, U30.3, U31.3, U32.3, U33.3, U34.3, U35.3, U36.3, U37.3, U38.3, U39.3, U40.3, U41.3, U42.3, U43.3, U44.3, U45.3, U46.3, U47.3, U48.3, U49.3, U50.3, U51.3, U52.3, U53.3, U54.3, U55.3, U56.3, U57.3, U58.3, U59.3, U60.3, U61.3, U62.3, U63.3, U64.3, U65.3, U66.3, U67.3, U68.3, U69.3, U70.3, U71.3, U72.3, U73.3, U74.3, U75.3, U76.3, U77.3, U78.3, U79.3, U80.3, U81.3, U82.3, U83.3, U84.3, U85.3, U86.3, U87.3, U88.3, U89.3, U90.3, U91.3, U92.3, U93.3, U94.3, U95.3, U96.3, U97.3, U98.3, U99.3, U100.3, U101.3, U102.3, U103.3, U104.3, U105.3, U106.3, U107.3, U108.3, U109.3, U110.3, U111.3, U112.3, U226.1, U226.3, W227.1, W230.1
Net_R1_2: R1.1, U226.4

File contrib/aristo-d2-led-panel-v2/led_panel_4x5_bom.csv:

Comment,Designator,Footprint,LCSC Part #
C14663_C0603,"C1, C10, C100, C101, C102, C103, C104, C105, C106, C107, C108, C109, C11, C110, C111, C112, C12, C13, C14, C15, C16, C17, C18, C19, C2, C20, C21, C22, C23, C24, C25, C26, C27, C28, C29, C3, C30, C31, C32, C33, C34, C35, C36, C37, C38, C39, C4, C40, C41, C42, C43, C44, C45, C46, C47, C48, C49, C5, C50, C51, C52, C53, C54, C55, C56, C57, C58, C59, C6, C60, C61, C62, C63, C64, C65, C66, C67, C68, C69, C7, C70, C71, C72, C73, C74, C75, C76, C77, C78, C79, C8, C80, C81, C82, C83, C84, C85, C86, C87, C88, C89, C9, C90, C91, C92, C93, C94, C95, C96, C97, C98, C99",C0603,C14663
C79111_CAP-SMD_L3.5-W2.8-R-RD,"C211, C212",CAP-SMD_L3.5-W2.8-R-RD,C79111
C42417599_LED-SMD_4P-L3.5-W3.5-TL_WS2812B_WS,"U1, U10, U100, U101, U102, U103, U104, U105, U106, U107, U108, U109, U11, U110, U111, U112, U12, U13, U14, U15, U16, U17, U18, U19, U2, U20, U21, U22, U23, U24, U25, U26, U27, U28, U29, U3, U30, U31, U32, U33, U34, U35, U36, U37, U38, U39, U4, U40, U41, U42, U43, U44, U45, U46, U47, U48, U49, U5, U50, U51, U52, U53, U54, U55, U56, U57, U58, U59, U6, U60, U61, U62, U63, U64, U65, U66, U67, U68, U69, U7, U70, U71, U72, U73, U74, U75, U76, U77, U78, U79, U8, U80, U81, U82, U83, U84, U85, U86, U87, U88, U89, U9, U90, U91, U92, U93, U94, U95, U96, U97, U98, U99",LED-SMD_4P-L3.5-W3.5-TL_WS2812B_WS,C42417599
C23138_R0603,R1,R0603,C23138
C502527_SOD-323_L1.8-W1.3-LS2.5-FD,D229,SOD-323_L1.8-W1.3-LS2.5-FD,C502527
C7484_SOT-23-5_L3.0-W1.7-P0.95-LS2.8-BR,U226,SOT-23-5_L3.0-W1.7-P0.95-LS2.8-BR,C7484
